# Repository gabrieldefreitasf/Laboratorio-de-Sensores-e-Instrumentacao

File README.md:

# Laboratorio-de-Sensores-e-Instrumentacao(LSI)
Repositório para códigos e arquivos de projeto referentes ao reflectômetro automatizado.<br>
Aqui estão códigos para ESP32 DevKit V1 escritos em framework Arduino para módulo de aquisição e controle do reflectômetro automatizado do LSI.<br>
Estão aqui os códigos separados por aquisição, movimento 2D, rotação e emulador para envio de dados.
Um código em python denominado ESP 32 - Datalogger é utilizado para gerar um arquivo com dados provenientes da serial.<br>
**Projeto desenvolvido no Laboratório de Sensores e Instrumentação do Departamento de Eletrônica e Sistemas da UFPE.**<br>
<br>
<br>
**Laboratory of Sensors and Instrumentation**<br>
Repository for codes and design files for the automated reflectometer.<br>
Here are the codes for ESP32 written in Arduino framework for LSI's automated reflectometer acquisition and control module.<br>
The codes are separated by acquisition, 2D movement, rotation and an emulator, for sending simulated data.<br>
A python code called ESP 32 - Datalogger is used to generate a file with data from the serial.<br>
**Project developed in the Laboratory of Sensors and Instrumentation under the Department of Electronics and Systems from UFPE.**<br>

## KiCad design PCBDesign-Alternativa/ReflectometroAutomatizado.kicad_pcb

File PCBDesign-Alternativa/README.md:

Este diretório abriga os arquivos de projeto para placa de circuito impresso do reflectômetro automatizado. Os arquivos foram gerados em plataforma KiCAD.
--------------------------------
This directory contains the design files for the printed circuit board for the automated reflectometer. The files were generated on KiCAD platform.

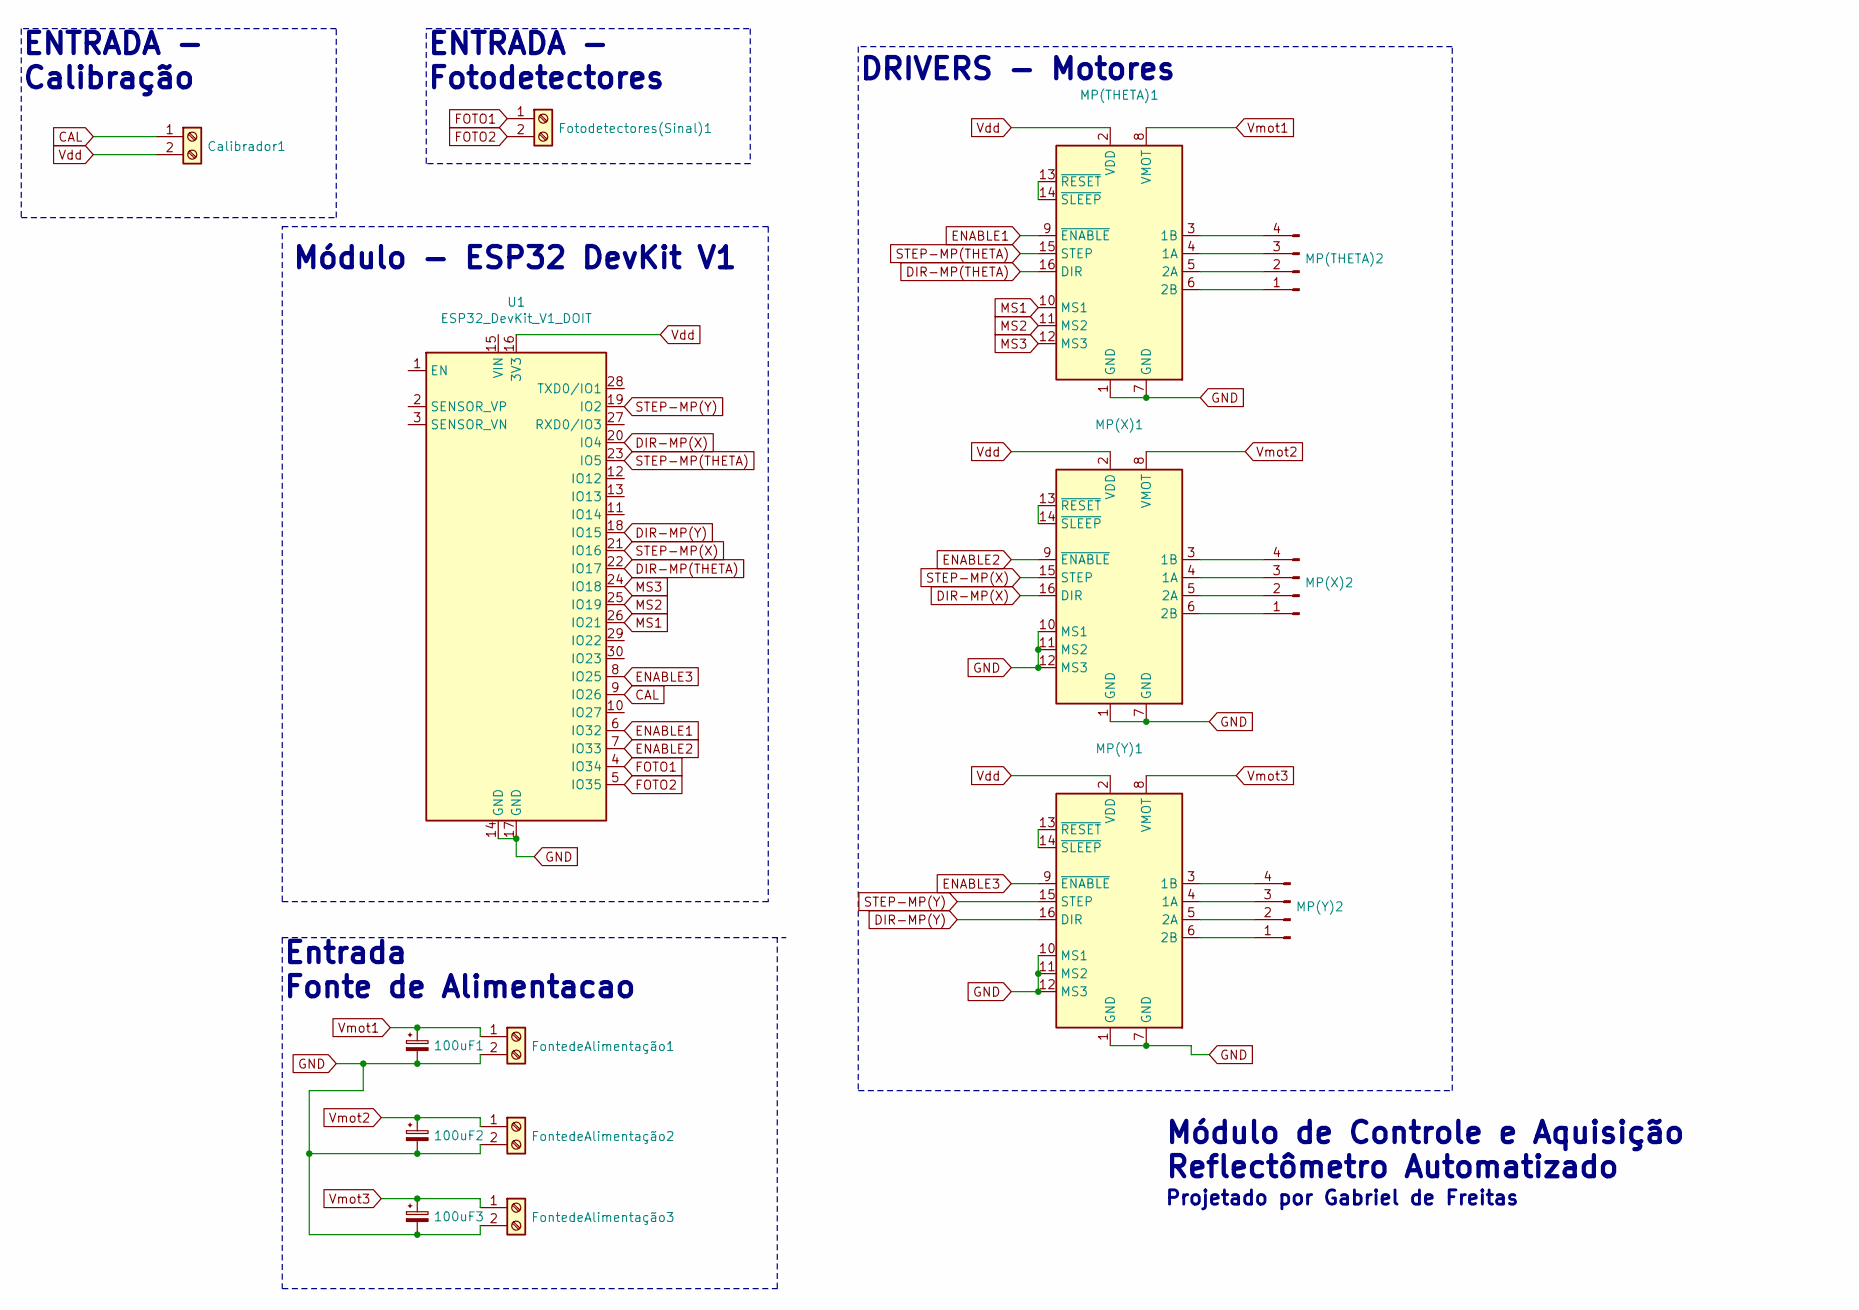
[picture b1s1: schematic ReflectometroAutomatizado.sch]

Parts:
100uF1, 100uF2, 100uF3: CP_Small; CP_Radial_D5.0mm_P2.00mm
Calibrador1: Screw_Terminal_01x02; TerminalBlock_bornier-2_P5.08mm
FontedeAlimentação1, FontedeAlimentação2, FontedeAlimentação3: Screw_Terminal_01x02; TerminalBlock_bornier-2_P5.08mm
Fotodetectores(Sinal)1: Screw_Terminal_01x02; TerminalBlock_bornier-2_P5.08mm
MP(THETA)1: Pololu_Breakout_A4988; MODULE_A4988
MP(THETA)2: Conn_01x04_Male; PinHeader_1x04_P2.54mm_Vertical
MP(X)1: Pololu_Breakout_A4988; MODULE_A4988
MP(X)2: Conn_01x04_Male; PinHeader_1x04_P2.54mm_Vertical
MP(Y)1: Pololu_Breakout_A4988; MODULE_A4988
MP(Y)2: Conn_01x04_Male; PinHeader_1x04_P2.54mm_Vertical
U1: ESP32_DevKit_V1_DOIT; esp32_devkit_v1_doit

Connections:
CAL: Calibrador1.1, U1.9 (IO26)
DIR-MP(THETA): MP(THETA)1.16 (DIR), U1.22 (IO17)
DIR-MP(X): MP(X)1.16 (DIR), U1.20 (IO4)
DIR-MP(Y): MP(Y)1.16 (DIR), U1.18 (IO15)
ENABLE1: MP(THETA)1.9 (~ENABLE), U1.6 (IO32)
ENABLE2: MP(X)1.9 (~ENABLE), U1.7 (IO33)
ENABLE3: MP(Y)1.9 (~ENABLE), U1.8 (IO25)
FOTO1: Fotodetectores(Sinal)1.1, U1.4 (IO34)
FOTO2: Fotodetectores(Sinal)1.2, U1.5 (IO35)
GND: 100uF1.2, 100uF2.2, 100uF3.2, FontedeAlimentação1.2, FontedeAlimentação2.2, FontedeAlimentação3.2, MP(THETA)1.1 (GND), MP(THETA)1.7 (GND), MP(X)1.1 (GND), MP(X)1.7 (GND), MP(X)1.10 (MS1), MP(X)1.11 (MS2), MP(X)1.12 (MS3), MP(Y)1.1 (GND), MP(Y)1.7 (GND), MP(Y)1.10 (MS1), MP(Y)1.11 (MS2), MP(Y)1.12 (MS3), U1.14 (GND), U1.17 (GND)
MS1: MP(THETA)1.10 (MS1), U1.26 (IO21)
MS2: MP(THETA)1.11 (MS2), U1.25 (IO19)
MS3: MP(THETA)1.12 (MS3), U1.24 (IO18)
unnamed: MP(THETA)1.3 (1B), MP(THETA)2.4
unnamed: MP(THETA)1.4 (1A), MP(THETA)2.3
unnamed: MP(THETA)1.5 (2A), MP(THETA)2.2
unnamed: MP(THETA)1.6 (2B), MP(THETA)2.1
unnamed: MP(THETA)1.13 (~RESET), MP(THETA)1.14 (~SLEEP)
unnamed: MP(X)1.3 (1B), MP(X)2.4
unnamed: MP(X)1.4 (1A), MP(X)2.3
unnamed: MP(X)1.5 (2A), MP(X)2.2
unnamed: MP(X)1.6 (2B), MP(X)2.1
unnamed: MP(X)1.13 (~RESET), MP(X)1.14 (~SLEEP)
unnamed: MP(Y)1.3 (1B), MP(Y)2.4
unnamed: MP(Y)1.4 (1A), MP(Y)2.3
unnamed: MP(Y)1.5 (2A), MP(Y)2.2
unnamed: MP(Y)1.6 (2B), MP(Y)2.1
unnamed: MP(Y)1.13 (~RESET), MP(Y)1.14 (~SLEEP)
STEP-MP(THETA): MP(THETA)1.15 (STEP), U1.23 (IO5)
STEP-MP(X): MP(X)1.15 (STEP), U1.21 (IO16)
STEP-MP(Y): MP(Y)1.15 (STEP), U1.19 (IO2)
Vdd: Calibrador1.2, MP(THETA)1.2 (VDD), MP(X)1.2 (VDD), MP(Y)1.2 (VDD), U1.16 (3V3)
Vmot1: 100uF1.1, FontedeAlimentação1.1, MP(THETA)1.8 (VMOT)
Vmot2: 100uF2.1, FontedeAlimentação2.1, MP(X)1.8 (VMOT)
Vmot3: 100uF3.1, FontedeAlimentação3.1, MP(Y)1.8 (VMOT)

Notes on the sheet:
DRIVERS - Motores
ENTRADA - Fotodetectores
Módulo - ESP32 DevKit V1
Entrada Fonte de Alimentacao
Módulo de Controle e Aquisição Reflectômetro Automatizado
Projetado por Gabriel de Freitas
ENTRADA - Calibração

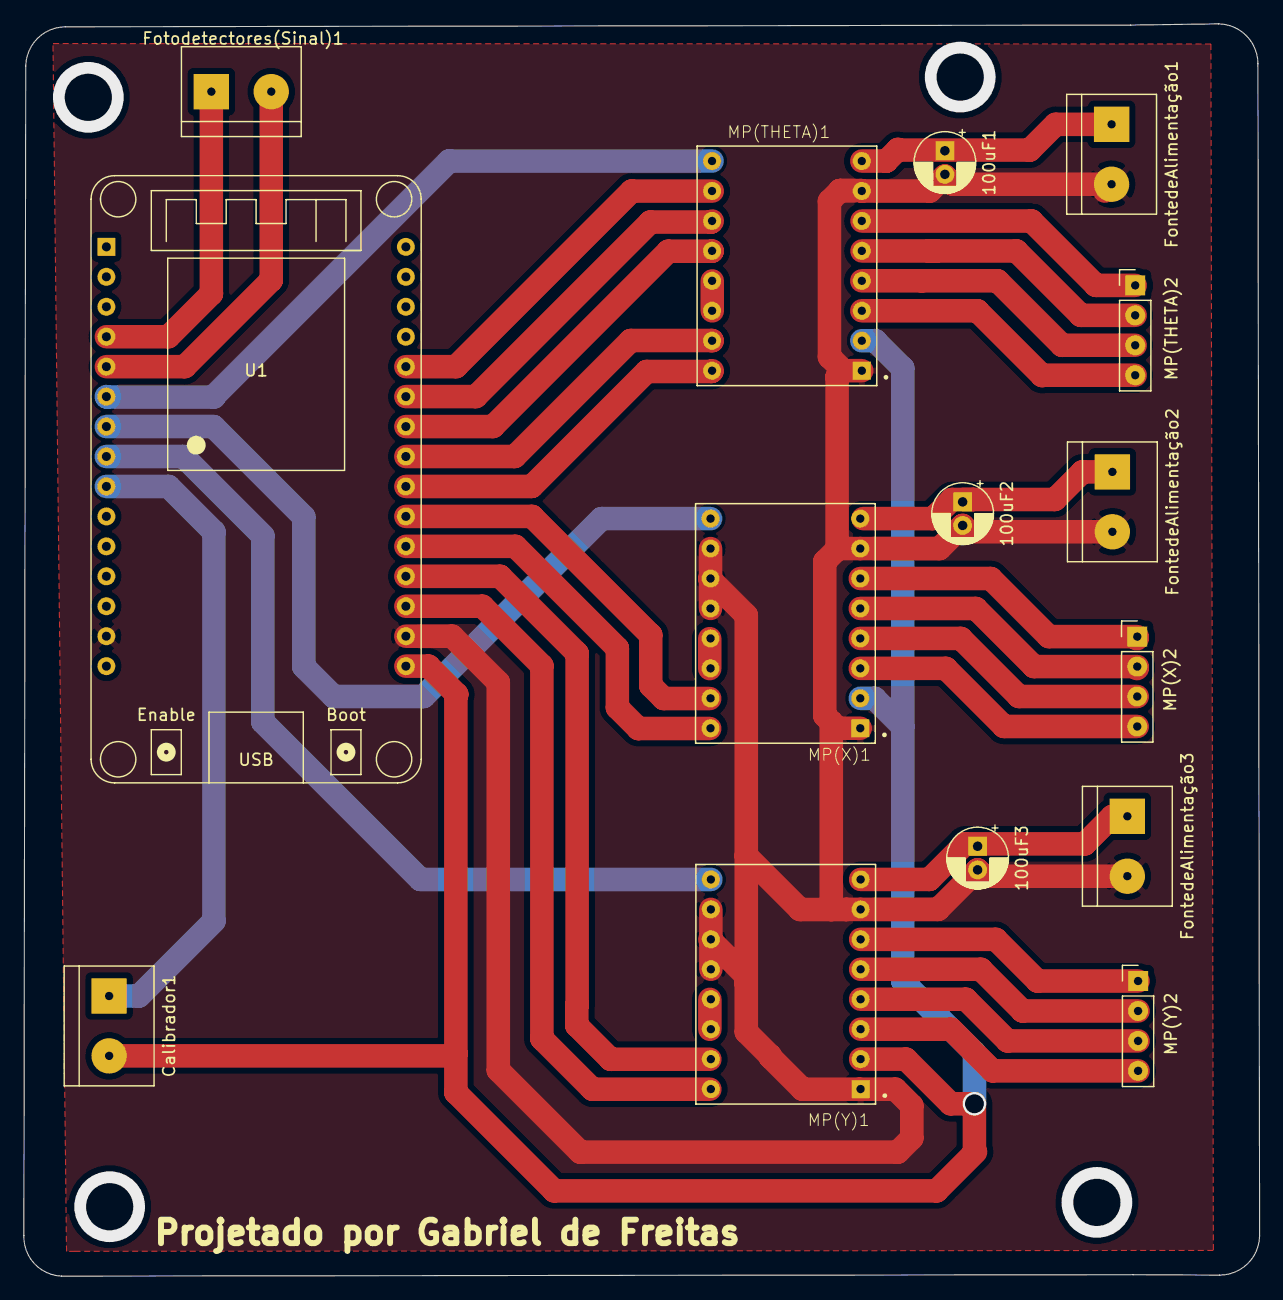
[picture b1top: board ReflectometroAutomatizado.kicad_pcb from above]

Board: 2 copper layers, 104.8 x 106.2 mm, 15 parts (0 on the bottom side), 35 nets.

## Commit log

2020-01-14 Add files via upload
    Código de aquisição de dados analógicos para ESP32.
2020-01-14 Create README.md
    Texto identificando o propósito do repositório e breve descrição dos arquivos aqui contidos.
2020-01-16 Update ESP32-Aquisicao.ino
    Excluída uma variável auxiliar sem utilidade
2020-01-18 Update ESP32-Rotacao.ino
    Reorganização da função setup e definição de parâmetros do prisma
2020-01-21 Update ESP32-Rotacao.ino
    Adição de cálculo de variáveis para translação necessária para manter o feixe no mesmo ponto e implementação da tal translação.
2020-02-03 Update ESP32-Aquisicao.ino
    Um delay retirado. Com isso, essa versão é, provavelmente, a final para a aquisição de dados podendo sofrer pequenas mudanças de adequação.
2020-02-12 Update ESP32-Rotacao.ino
    Casting adicionado nos dois laços for
2020-02-18 Update ESP32-Rotacao.ino
    Adição da variável theta_atual. Essa variável guarda o ângulo em que o sistema está e vai ser usada para construção do gráfico da reflectância em função do ângulo.
2020-02-18 Create CódigoPrincipal.ino
    Código que será a rotina principal executada pela ESP32. Por hora, constam as etapas de aquisição e rotação.
2020-02-18 Rename CódigoPrincipal.ino to ESP32-CódigoPrincipal.ino
    Padronizando o nome do arquivo.
2020-03-13 Update ESP32-Rotacao.ino
    Modificação nas portas por questão de praticidade das conexões. Adição de valores númericos nos parâmetros do prisma.
2020-03-13 Update ESP32-CódigoPrincipal.ino
    Modificação de portas por fins de praticidade de conexões. Atribuição de valores nos parâmetros do prisma.
2020-03-17 Create ESP32-Datalogger
    Script em python para ler dados provenientes de porta serial e salvá-los em arquivo .txt
2020-04-01 Código para movimento 2D baseado em driver a4988.
    Código recebe célula do usuário, movimenta bidimensionalmente e atualiza a posição. Essa versão inicial está implementado o movimento para a célula 60 apenas.
2020-04-02 Célula 59
    Adicionada rotina para movimentação até a célula 59
2020-04-02 Declaração de células 55 a 76.
    Montando a matriz apenas declarando as variáveis de posição por enquanto, para ter idéia da memória necessária sem gastar muito tempo. As células aqui declaradas correspondem às linhas 19 e 18 desse 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
2020-04-02 Declaração das células 77 à 98
    Declaração das células presentes nas linhas 17 e 16.
2020-04-03 Declaração das células 99 à 120.
    Descritas as posições para as células que constam nas linhas 15 e 14 desse código.
2020-04-03 Declaração das células 33 à 54
    Linhas 20 e 21 desse código.
2020-04-04 Declaração das células 0 a 21
    Linhas 23 e 24 desse código. Observando que o uso de memória em percentual para declarar duas variáveis float para cada célula não foi grande, vou manter essa idéia do código. Rotina para movimentaçã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
2020-04-07 Modificação de erros de cálculo
    Correção do sinal do valor de translação e adição do valor absoluto no for de movimentação dos motores.
2020-04-07 Correção nos for de movimentação dos motores
    Adição da função abs nos for de movimentação.
2020-04-07 Rotina de movimento para células 55 a 76
    Adicionado código para movimentação para células que constam nas linhas 20 e 21 desse código.
2020-04-08 Correção dos for de movimentação
    Havia um erro simples com os parenteses.
2020-04-08 Código de movimento para as células 77 à 87
    Linha 19 desse código.
2020-04-09 Código movimentação para células 88 a 98
    Linha 8
2020-04-09 Código de movimentação para células 99 a 109
    Linha 17
2020-04-09 Código de movimentação para células 110 a 120
    Linha 16
2020-04-10 Código de movimentação para as células 33 a 54
    Linhas 22 e 23.
2020-04-10 Código para movimentação das células 0 à 32
    Linhas 24, 25 e 26.
2020-04-10 Adição da função de movimento 2D
    Função void ir_para(int celula)
2020-04-15 Alteração das portas da ESP
2020-04-19 Update ESP32-CódigoPrincipal.ino
    - Alteração dos ângulo internos do prisma alpha,beta,gama=60°
    rotacionar()
    - Intervalos de subdivisão de passo
    - Atualização da variável x devido a correção
    ir_para()
    -Alteração de x=posicaoi_x-x -> x = posicaoi_x (idem y) i=120,119...
2020-04-19 Update ESP32-Movimento2D.ino
    Alteração x = posicao[i]_x-x; -> x = posicao[i]_x;
2020-06-16 Modificação na função loop
    Linhas 4518-1522. Os dados floats são convertidos em string e enviados serialmente como a string dados[17].
2020-06-18 Código agora gera arquivo csv ao inves de txt
    Gera csv e data agora é recebido como uma string
2020-07-16 Emulador de Reflectômetro (Dados Seriais)
    Emula envio de dados do tipo "Ângulo;Reflectância" via serial. Esse código é útil para testar a geração de arquivos por python.
2020-07-27 Correção das funções matemáticas
    Cálculo de d estava incorreto. Argumento da função asin() deve estar entre [-pi/2;pi/2].
2020-07-27 Código gera txt com dados
    Resulta em arquivo txt com dados do tipo theta:reflectancia, um ponto em cada linha.
2020-07-28 Correção na identificação de translado negativo/positivo
2020-08-11 Uso da função pinMode
    Adicionado uso da função pinMode para garantir funcionamento da função digitalWrite.
2021-06-03 Uso da função abs()
    Uso da função abs() na comparação para subdivisão de passo.
2021-08-30 Atualização de valores de calibração
    Valores de calibração para MP(theta) e MP(x) foram atualizados.
2021-08-31 Correção de valores de calibração
    Valores anteriormente em graus e agora em radiano.
2021-09-03 Correção de funções for para passo de motor.
    As funções estavam com valores desatualizados de constantes de calibração.
2021-12-13 Create PCBDesign-Alternativa
2021-12-13 Diretório para versão alternativa de PCB
2021-12-13 Projeto da V2 da PCB
    Este projeto inclui controle de enable dos drivers e alimentação separada para cada motor.
2021-12-13 Rename ESP32-Aquisicao.ino to Códigos-ESP32/ESP32-Aquisicao.ino
2021-12-13 Rename ESP32-CódigoPrincipal.ino to Códigos-ESP32/ESP32-CódigoPrincipal.ino
2021-12-13 Rename ESP32-Movimento2D.ino to Códigos-ESP32/ESP32-Movimento2D.ino
2021-12-13 Rename ESP32-Rotacao.ino to Códigos-ESP32/ESP32-Rotacao.ino
2021-12-13 Rename Emulador.ino to Códigos-ESP32/Emulador.ino
2021-12-13 Datalogger em python.
    Datalogger para ser rodado no computador de laboratório.
2021-12-13 Código para calibração automática
2021-12-13 Cabeçalho atualizado
2021-12-13 Remoção de caractere maiusculo da varial "DirPinx"
2021-12-13 Atualização de cabeçalho
2022-02-21 Projeto da placa atualizada
    Projeto com enable e alimentação isolada para motores
